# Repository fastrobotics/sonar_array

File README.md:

# Sonar Array
__TOC__
- [Overview](#overview)
- [Project Plan](#project-plan)
- [Lexicon](#lexicon)
- [Literature Review](#literature-review)
- [Boards](#boards)
- [Communication](#communication)
- [Sensors](#sensors)
- [Nodes](#nodes)
- [Sonar Array Package](#sonar-array-package)
- [Troubleshooting](#troubleshooting)

## Overview
The Sonar Array project is designed to study and create an advanced sensor array that can use COTS sonar sensors to build a map of a robot's surroundings.

The Sonar Array will be composed of the following:
- Multiple [Parallax Ping Ultrasonic Distance Sensors](doc/Sensors/PingUltraSonicDistanceSensor/PingUltraSonicDistanceSensor.md).
- A mounting hardware design to provide the following mounting options:
  - A fully contained Sonar Array
  - Hardware designed to mount sonar sensors to specific locations on your robot
- Software Driver running on a Board to use the Sonar Sensors, along with a ROS Node that can communicate with the Board that publishes this data over ROS.
- Visualization tools used to see the Sonar Array in action

## Project Plan
| Status | Epic |
| --- | --- |
| STARTED | [Sonar Sensor Characterization](https://dev.azure.com/davidgitz/Sonar%20Array/_workitems/edit/1443) |
| STARTED | [Sonar Array Driver](https://dev.azure.com/davidgitz/Sonar%20Array/_workitems/edit/1438) |
| NOT STARTED | [Sonar Array Hardware Design & Build](https://dev.azure.com/davidgitz/Sonar%20Array/_workitems/edit/1442) |
| NOT STARTED | [Sonar Array Simulation](https://dev.azure.com/davidgitz/Sonar%20Array/_workitems/edit/1445) |
| NOT STARTED | [Sonar Array Driver Optimization](https://dev.azure.com/davidgitz/Sonar%20Array/_workitems/edit/1439) |
| NOT STARTED | [RVIZ Sonar Array Plugin](https://dev.azure.com/davidgitz/Sonar%20Array/_workitems/edit/1440) |
| NOT STARTED | [Occupancy Grid](https://dev.azure.com/davidgitz/Sonar%20Array/_workitems/edit/1441) |
| NOT STARTED | [Sonar Array Driver Scan/Ping Pattern Automation](https://dev.azure.com/davidgitz/Sonar%20Array/_workitems/edit/1444) |

## [Lexicon](Lexicon.md)
## [Literature Review](doc/LiteratureReview/LiteratureReview.md)
## [Boards](doc/Boards/Boards.md)
## [Communication](doc/Communication/Communication.md)
## [Sensors](doc/Sensors/Sensors.md)
## [Nodes](doc/Nodes/Nodes.md)

## Sonar Array Package

## [Troubleshooting](doc/Troubleshooting/Troubleshooting.md)

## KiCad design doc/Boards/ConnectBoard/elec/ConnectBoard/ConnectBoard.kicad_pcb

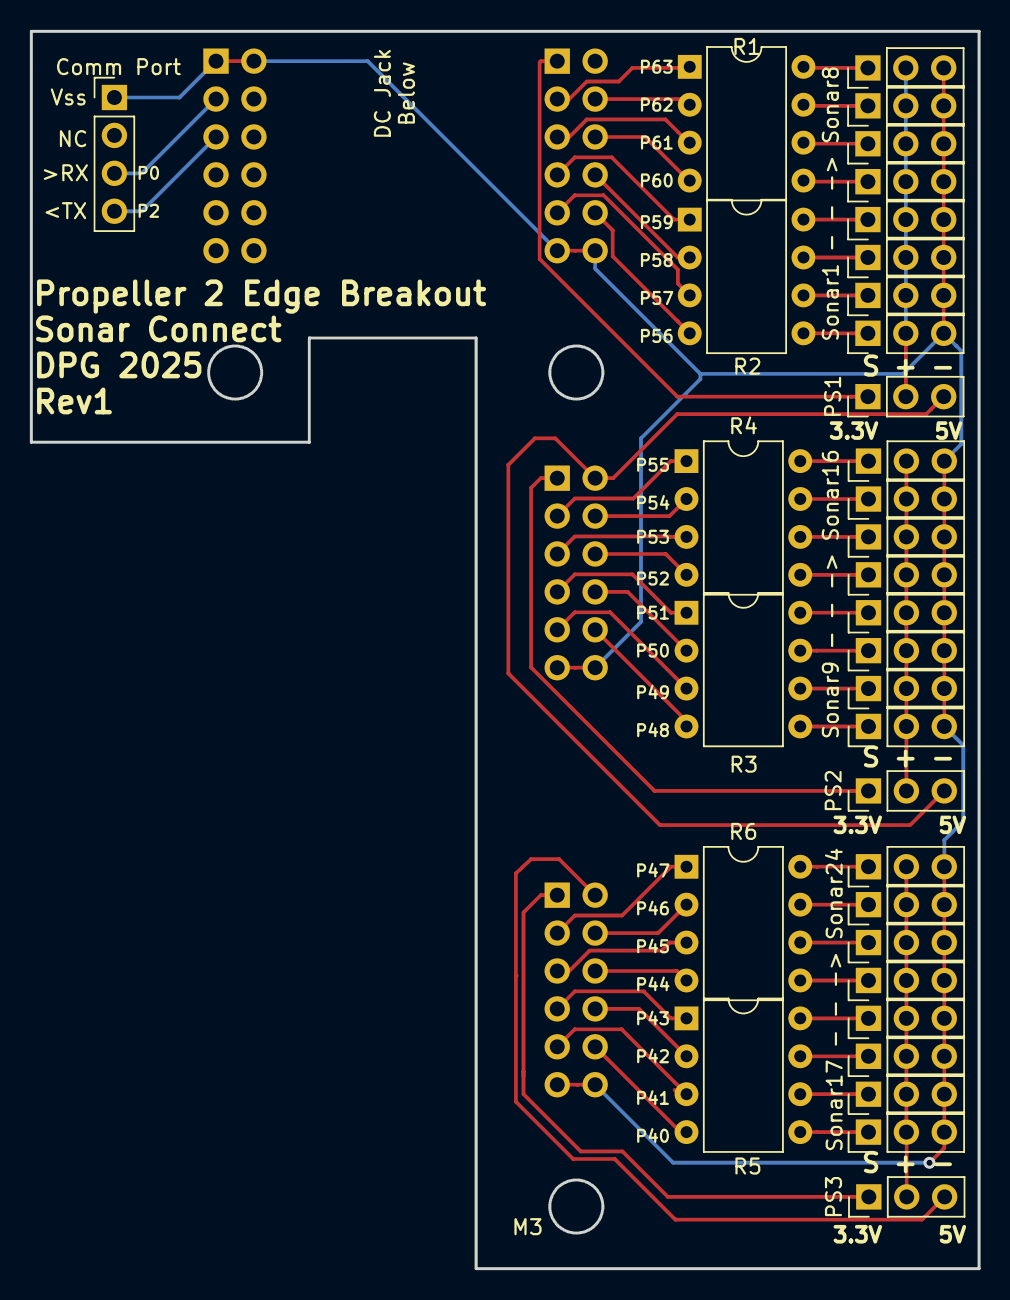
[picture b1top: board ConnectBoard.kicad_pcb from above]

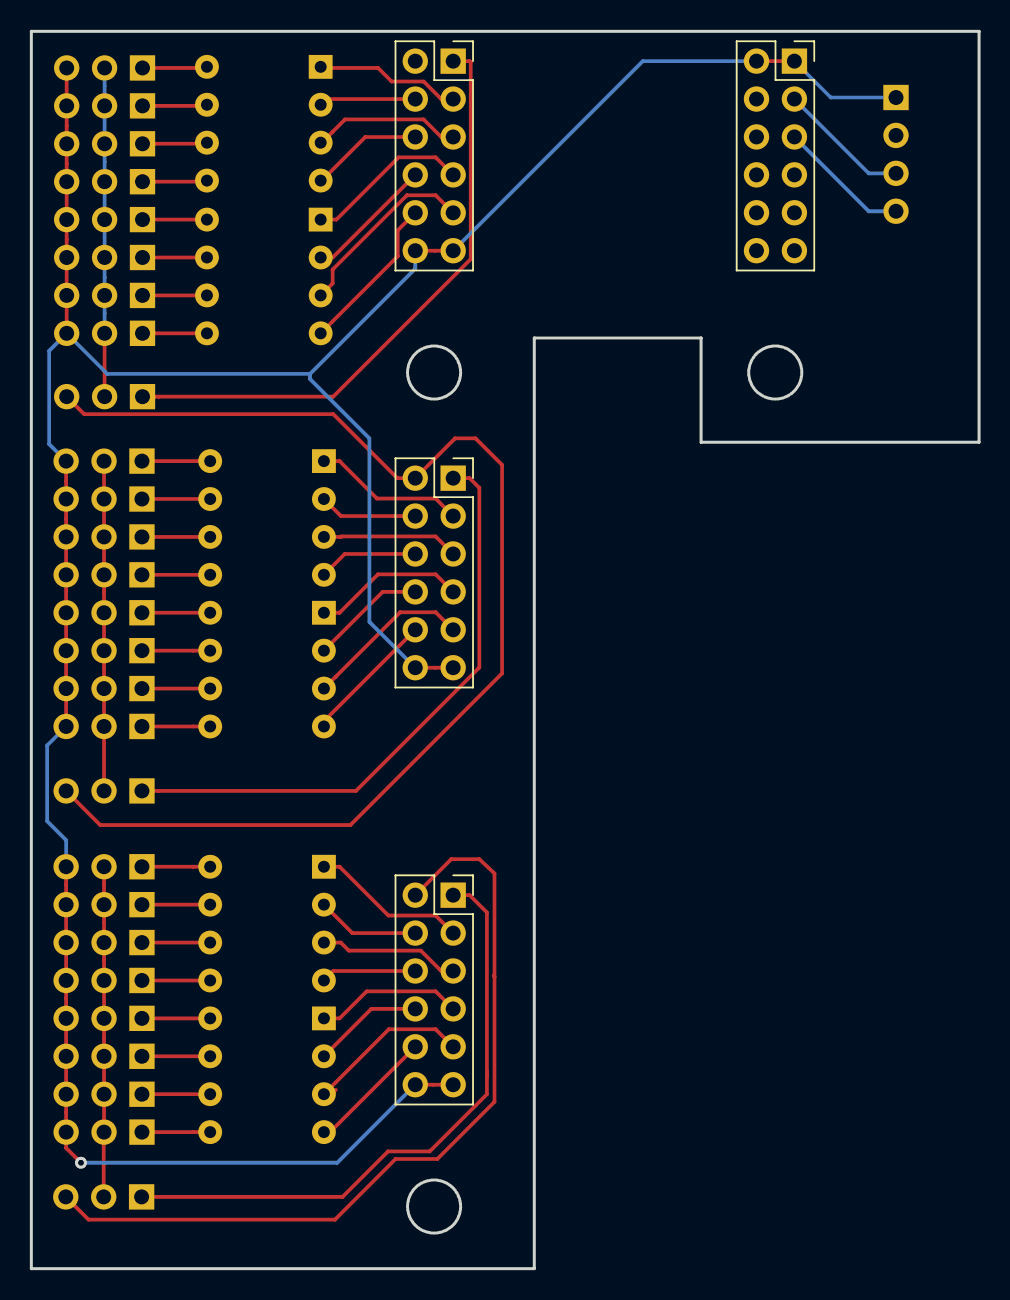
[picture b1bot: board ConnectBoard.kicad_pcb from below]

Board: 2 copper layers, 63.5 x 82.9 mm, 38 parts (4 on the bottom side), 59 nets.

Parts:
Conn1, Conn2, Conn3, Conn4: PropEdgeConnect; PinSocket_2x06_P2.54mm_Vertical
J0: Comm Port; PinHeader_1x04_P2.54mm_Vertical
PS1, PS2, PS3: PowerSelect; PinHeader_1x03_P2.54mm_Vertical
R1, R2: 4.7k; DIP-8_W7.62mm
R3, R4, R5, R6: R_Pack04_Split; DIP-8_W7.62mm
S1, S2, S3, S4, S5, S6, S7, S8, S9, S10, S11, S12, S13, S14, S15, S16, S17, S18, S19, S20, S21, S22, S23, S24: SonarConnect; PinHeader_1x03_P2.54mm_Vertical

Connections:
+5V1: Conn3.2, PS1.3, PS2.3
+5V3: Conn4.2, PS3.3
/P0: Conn1.3, J0.3
/P2: Conn1.5, J0.4
/P40: Conn4.10, R5.4
/P41: Conn4.9, R5.3
/P42: Conn4.8, R5.2
/P43: Conn4.7, R5.1
/P44: Conn4.6, R6.4
/P45: Conn4.5, R6.3
/P46: Conn4.4, R6.2
/P47: Conn4.3, R6.1
/P48: Conn3.10, R3.4
/P49: Conn3.9, R3.3
/P50: Conn3.8, R3.2
/P51: Conn3.7, R3.1
/P52: Conn3.6, R4.4
/P53: Conn3.5, R4.3
/P54: Conn3.4, R4.2
/P55: Conn3.3, R4.1
/P56: Conn2.10, R2.4
/P57: Conn2.9, R2.3
/P58: Conn2.8, R2.2
/P59: Conn2.7, R2.1
/P60: Conn2.6, R1.4
/P61: Conn2.5, R1.3
/P62: Conn2.4, R1.2
/P63: Conn2.3, R1.1
GND: Conn1.1, Conn1.2, Conn2.11, Conn2.12, Conn3.11, Conn3.12, Conn4.11, Conn4.12, J0.1, S1.3, S2.3, S3.3, S4.3, S5.3, S6.3, S7.3, S8.3, S9.3, S10.3, S11.3, S12.3, S13.3, S14.3, S15.3, S16.3, S17.3, S18.3, S19.3, S20.3, S21.3, S22.3, S23.3, S24.3
unnamed: PS1.2, S1.2, S2.2, S3.2, S4.2, S5.2, S6.2, S7.2, S8.2
unnamed: PS2.2, S9.2, S10.2, S11.2, S12.2, S13.2, S14.2, S15.2, S16.2
unnamed: PS3.2, S17.2, S18.2, S19.2, S20.2, S21.2, S22.2, S23.2, S24.2
unnamed: R1.5, S5.1
unnamed: R1.6, S6.1
unnamed: R1.7, S7.1
unnamed: R1.8, S8.1
unnamed: R2.5, S1.1
unnamed: R2.6, S2.1
unnamed: R2.7, S3.1
unnamed: R2.8, S4.1
unnamed: R3.5, S9.1
unnamed: R3.6, S10.1
unnamed: R3.7, S11.1
unnamed: R3.8, S12.1
unnamed: R4.5, S13.1
unnamed: R4.6, S14.1
unnamed: R4.7, S15.1
unnamed: R4.8, S16.1
unnamed: R5.5, S17.1
unnamed: R5.6, S18.1
unnamed: R5.7, S19.1
unnamed: R5.8, S20.1
unnamed: R6.5, S21.1
unnamed: R6.6, S22.1
unnamed: R6.7, S23.1
unnamed: R6.8, S24.1
V40: Conn4.1, PS3.1
V48: Conn3.1, PS2.1
V56: Conn2.1, PS1.1

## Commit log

2025-03-07 Initial commit.
2025-03-08 Added board info.
2025-03-08 Defined initial protocol specs. Requires validation with hardware.
2025-03-08 deploy: 162ac9027cc478212be0d3d483a01b04cfbb5022
2025-03-08 deploy: a51ae8fb67e056faa3875880b621de8ff19b7dbe
2025-03-08 Draft
2025-03-08 Updaes
2025-03-09 Added cli option for exec driver.
2025-03-12 Added node. Node does not call in to driver yet.
2025-03-12 Create HelloWorld.spin2
    WIP
2025-03-13 Updates
    Added some examples, documentation. Nothing working yet.
2025-03-13 Removed redundant docs
2025-03-14 Preliminary Board code
2025-03-14 Dummy Data send from Board
2025-03-14 Start working on Sonar Board Packet Parser.
2025-03-15 deploy: 8f89c29f35731a535b212dc7d2e7af09af6a43f4
2025-03-16 Lit Review Complete.
2025-03-16 deploy: ceeb12cf9d9adbebb599e057c0a085d08be9fd03
2025-03-17 Added Lexicon.
2025-03-17 deploy: 265f92f0ce471ef363db8907934c5d9bca265bb2
2025-03-17 Major work complete. Review action items left.
2025-03-18 Updated exec driver to allow number of sonars input.
2025-03-18 Board updates
2025-03-18 Updated dummy code
2025-03-18 Board and Node updates.
2025-03-18 deploy: eb1b34b40d7259e833fae3d0c301a5f2406aa038
2025-03-19 Added info on Semaphores
2025-03-19 Changed Board code to use mm units
2025-03-19 deploy: 4444e2cd13e372500f5710f79ec211b95b373020
2025-03-19 Bracket CAD design complete.
2025-03-20 Updated puml docs.
2025-03-20 Updated mock.
2025-03-20 deploy: eb07f2993a7e685489c880fcbff96a8a876bac4e
2025-03-20 Working on user config. Next need to load it.
2025-03-21 Updated tests.
2025-03-21 deploy: 1dd4c5478295d4054cca997b143080ec0427ff8f
2025-03-23 Working on board outline
2025-03-23 Added
2025-03-23 Updated board
2025-03-23 Testing comm/debug ports
2025-03-24 More work on this.
2025-03-25 Adding documentation.
2025-03-25 Minor updates
2025-03-26 Updated diagnostics strategy.
2025-04-01 Major work done.
2025-04-01 Updates.
2025-04-01 deploy: 95ba72681b1e1d554de55b3c5785fb691b637337
2025-04-02 Refactoring diagnostics.
2025-04-06 Working on testing.
2025-04-08 Fixed pin definition
2025-04-08 Some updates
2025-04-09 Work Complete
2025-04-09 deploy: bdb1150a5e918a12635acadded6517901c08bdc6
2025-04-09 Testing on bot.
